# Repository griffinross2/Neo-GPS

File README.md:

# Neo-GPS
Neo-GPS is my second take on creating a custom GPS receiver, taking into account the lessons I learned previously and seeking to do everything as custom as possible.

## Disclaimer
This project was made for my own learning and interest. It is NOT a professional implementation of a GPS receiver nor is it ever likely to be in a complete or reliable state.
It should be used for your learning and interest too, not for any real-world use.

## Goals
* Fully-functioning GPS L1 C/A receiver.
* Custom implementation of HDL and firmware modules wherever practical.
* Testing infrastructure with testbenches for all modules.
* Use of open-source software and tools (e.g. avoid Vivado until synthesis, instead using Verilator for simulation).

## Basic Implementation Concepts
To demodulate and track, we need fast real-time hardware, so an FPGA is the best choice. However, decoding ephemeris and solving the navigation equations requires memory and complex
calculations so this should be done on a microcontroller. This means we need the microcontroller to control the tracking channels in the FPGA to start tracking satellites and to get
timing and navigation data to do its decoding and solving. This will happen through SPI, with the FPGA presenting registers to be read/written.

This split architecture was used by [Andrew Holme](http://www.aholme.co.uk/GPS/Main.htm) whose custom GPS receiver project is a major source of inspiration and knowledge for this one.

The FPGA itself receives samples of an IF downconverted from the L1 band (1.57542 GHz). Because I am neither smart enough nor brave enough to attempt my own GPS RF frontend design,
I am using the [MAX2769](https://www.analog.com/en/products/max2769.html) GPS receiver IC. This chip contains an LNA, PLL, ADCs, and the other associated components that downconvert 
and then sample the signal. Up to 2-bit I and 2-bit Q samples are then presented to the FPGA along with the sampling clock.

I will also implement a micro-SD logger on the FPGA to log raw samples and/or other data for testing purposes.

## Usage
This project is split into several directories:

### Hardware
This folder contains KiCAD projects and libraries. There is a frontend board used with the FPGA dev board, an SD card board also used with the FPGA, and a project for the full custom board.
As of writing, only the frontend is in use. The SD card board was not ordered, and the full custom board is in development still. Use KiCAD 10.

### Simulation
This is a C++ simulation of a GPS receiver supporting GPS L1 C/A and Galileo E1 currently. It takes in a binary signal recording file which is just 1-bit I samples packed little-endian.
Samples are not included, but I may add a link to some at some point. The core of the simulator in `src/` and `inc/` is compiled as a library. The examples in `tests/` use it, including
`solve` which is a full simulation of acquisition, tracking, and solving for position using GPS and Galileo. The simulation depends on FFTW (included) and Eigen (installed by CMake).

To build and run, make sure you have a modern C++ compiler and CMake installed. Use CMake to build and run on of the test targets. It should install the needed dependencies automatically.
This software has only been tested on Windows but should work elsewhere.

### RTL
The RTL directory contains the RTL for the FPGA which, for testing, was a Spartan-7 on an Arty S7-50 board. `src/` contains modules. `testbench/` contains top-level testbenches for simulation. 
`top/` contains top-level files used with Vivado for on-board testing. `constraints/` contains .xdc constraints files for Vivado. `verilator/` contains CMake files and C++ testbenches for 
simulating with Verilator. `scripts/` contains TCL scripts for running Vivado.

To simulate with Verilator, first make sure you have a working installation of Verilator and CMake. Make sure the VERILATOR_ROOT environment variable is set. Then use the `verilator.py` script. 
This script helps to build and run the testbenches. Setting up a new testbench requires making one in `testbenches/` and a corresponding `CMakeLists.txt` and `sim_main.cpp` in the `verilator/`
folder. Use the examples given as a template.

To synthesize using Vivado, first make sure yuou have Vivado installed. I then added it to my PATH, but you could use the path to it directly in `vivado.py`. If you are making a new top-level
file, add it to `top/` and make a corresponding TCL script in `scripts/`. Then you can use the python script to initialize Vivado with the project. You will probably want to use the `-g` option
to actually open the Vivado GUI, unless you set it up to do everything automatically using the TCL script.

### RP2350
This folder contains the code used with Raspberry Pi Pico 2 board for testing. The Pi Pico SDK is pulled in as a Git submodule. Make sure you pull that and also install the Arm GNU Toolchain.
Then, you can modify `CMakeUserPresets.json` with your path to the toolchain or setup your own CMake configuration. Then just use CMake to build.

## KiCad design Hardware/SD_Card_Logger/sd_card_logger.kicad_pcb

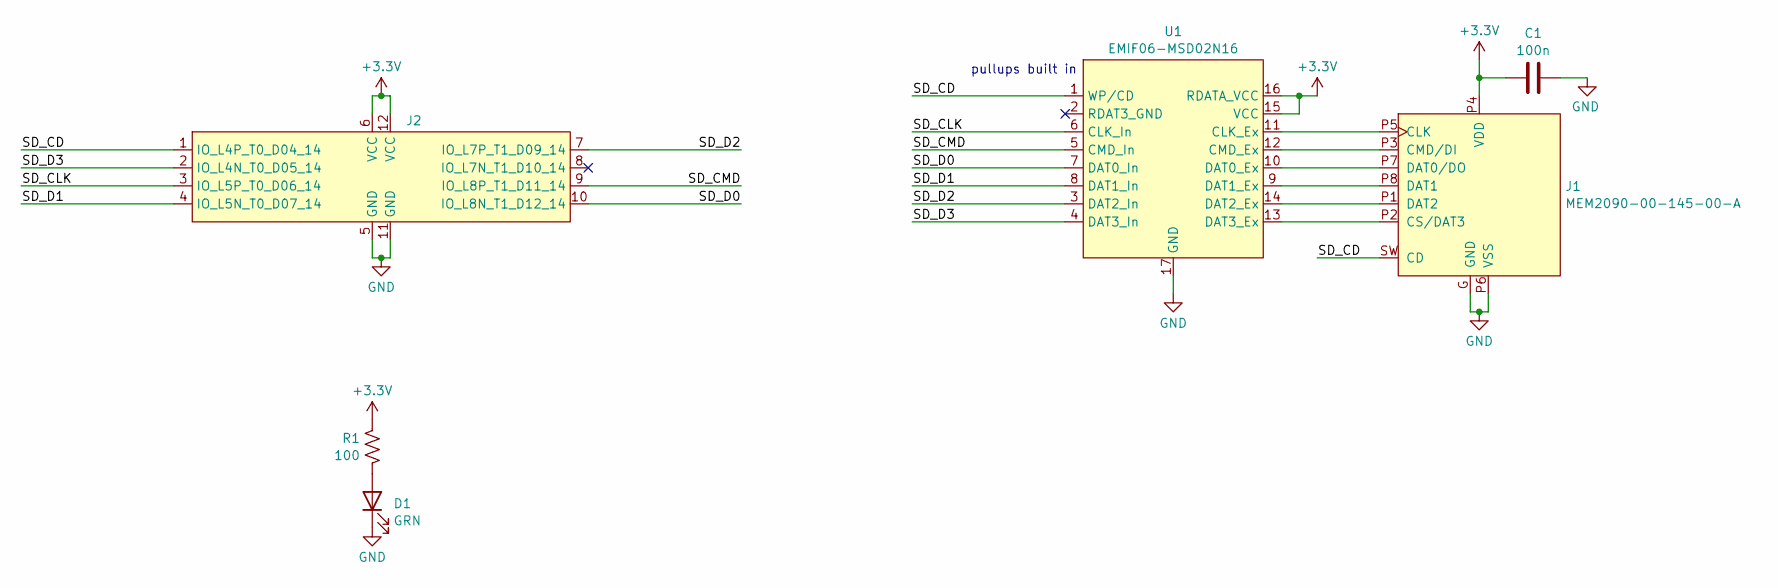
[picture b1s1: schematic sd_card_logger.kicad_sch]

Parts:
C1: 100n; C_0805_2012Metric; Manufacturer_Part_Number GCJ188R71H104KA12D
D1: GRN; LED_0805_2012Metric
J1: MEM2090-00-145-00-A; GCT_MEM2090-00-145-00-A_REVA; PARTREV A
J2: PinHeader_2x06_P2.54mm_Horizontal_Pmod
R1: 100; R_0805_2012Metric
U1: EMIF06-MSD02N16

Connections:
+3.3V: C1.1, J1.P4 (VDD), J2.6 (VCC), J2.12 (VCC), R1.1, U1.15 (VCC), U1.16 (RDATA_VCC)
/SD_CD: J1.SW (CD), J2.1 (IO_L4P_T0_D04_14), U1.1 (WP/CD)
/SD_CLK: J2.3 (IO_L5P_T0_D06_14), U1.6 (CLK_In)
/SD_CMD: J2.9 (IO_L8P_T1_D11_14), U1.5 (CMD_In)
/SD_D0: J2.10 (IO_L8N_T1_D12_14), U1.7 (DAT0_In)
/SD_D1: J2.4 (IO_L5N_T0_D07_14), U1.8 (DAT1_In)
/SD_D2: J2.7 (IO_L7P_T1_D09_14), U1.3 (DAT2_In)
/SD_D3: J2.2 (IO_L4N_T0_D05_14), U1.4 (DAT3_In)
GND: C1.2, D1.1 (K), J1.G (GND), J1.P6 (VSS), J2.5 (GND), J2.11 (GND), U1.17 (GND)
unnamed: D1.2 (A), R1.2
unnamed: J1.P5 (CLK), U1.11 (CLK_Ex)
unnamed: J1.P3 (CMD/DI), U1.12 (CMD_Ex)
unnamed: J1.P2 (CS/DAT3), U1.13 (DAT3_Ex)
unnamed: J1.P7 (DAT0/DO), U1.10 (DAT0_Ex)
unnamed: J1.P8 (DAT1), U1.9 (DAT1_Ex)
unnamed: J1.P1 (DAT2), U1.14 (DAT2_Ex)

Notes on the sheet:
pullups built in

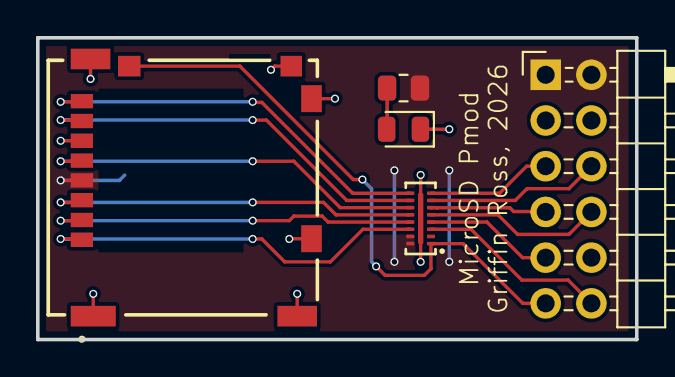
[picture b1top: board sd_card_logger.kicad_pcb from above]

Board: 2 copper layers, 33.3 x 16.8 mm, 6 parts (1 on the bottom side), 16 nets.

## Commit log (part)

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2026-05-03 Add kicad projects back and setup verilator simulation
2026-05-03 Waveform files from verilator
2026-05-04 Add script for gtkwave
2026-05-04 Switch the mingw for FST trace files, more reorganization and add spi_tx and l1ca_code generator
2026-05-06 Change to GPL-3
2026-05-09 Start on SD card host by making module for the CMD line of the SD bus
2026-05-09 Finish SD card logger PCB and reorganize RTL a bit
2026-05-10 SD card data module
2026-05-11 Integrate fake SD model and implement CMD0 and CMD8 of initialization
2026-05-12 Add CRC7 module and finish initialization commands
2026-05-12 Add wide bus mode to initialization
2026-05-12 Data transmission
2026-05-15 SD logger top module thru Vivado
2026-06-07 Add in some software simulation stuff and the AC PCA search
2026-06-07 oops
2026-06-13 Complete logger, and optimize writes by using a larger buffer and multi-block write
2026-06-13 Further increase logger performance using pre-erase hint ACMD23
    - Seems like the logger no longer overruns the FIFO when logging 1-bit I at 19.2 MSPS
2026-06-15 Frontend config module to configure MAX2769 through its serial interface
